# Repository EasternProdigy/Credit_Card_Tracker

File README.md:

# Wallet tracker card: handoff package (rev 0.5, 2026-11-13)

## How to use this
1. Copy everything in this folder into your KiCad project folder (e.g. `~/Desktop/PCB/<project>/`).
2. `CLAUDE.md` goes in the project root. Claude Code reads it automatically.
3. Set up git and the secret scanner once: `bash scripts/install_git_hooks.sh`, then `git add . && git commit -m "Add design handoff package rev 0.5"`
4. Start Claude Code in that folder and say: **"Read CLAUDE.md and docs/00_START_HERE.md, then start step 1."**

## Contents
- `CLAUDE.md`: role, rules and workflow for the KiCad Claude
- `docs/`: requirements, architecture, schematic spec, layout constraints, stackup, firmware, server, verification plan, open items, decision log
- `design/`: `netlist.yaml` (every part and net), `bom_v1.csv`, `bom_v2.csv`, `values_calc.py`
- `sims/`: every simulation and verification script, plus `results/` JSON
- `reports/`: research report and verification report
- `plots/`: simulation plots
- `server/`: Traccar config used in the backend test

## Rerun the sims on Fedora
```
sudo dnf install ngspice
pip install --user PyNEC numpy scipy matplotlib cryptography ecdsa pycryptodomex requests
cd sims && python3 qi_coupling.py && python3 power_path_ngspice.py   # etc.
```
`protocol_roundtrip.py` needs `git clone https://github.com/leonboe1/GoogleFindMyTools /tmp/src/GoogleFindMyTools`.
`backend_e2e.py` needs Traccar running with `server/traccar.xml`.

Design review page (3D model, floorplan, face, schematic draft): https://claude.ai/artifact/XV6vFWMy8m2t3a1oJFXLs5

## Auto-logging (open-source build log)
Every Claude Code session in this folder logs itself:
- `.claude/settings.json` registers two hooks. **SessionStart** loads the latest log so each session picks up where the last left off. **Stop** blocks Claude from finishing a turn if it changed files without writing to `docs/log/<today>.md`, or if raw data is sitting in `measurements/inbox/`.
- Drop PPK2 exports, NanoVNA `.s1p` files, scope screenshots and photos into `measurements/inbox/`. Claude files each into `measurements/<date>/` with a note and logs it (`scripts/log_measurement.py`).
- Tell Claude test results in plain words too; the rules in `CLAUDE.md` make it log them.
- Secrets live in `secrets/` (git-ignored), and the pre-commit hook runs gitleaks.
- Use the same folder (and `CLAUDE.md`) for the firmware, server and app sessions, under `firmware/`, `server/` and `app/`, so all of them write to one log.

Before making the repo public: pick licenses (common choice: CERN-OHL-S-2.0 for hardware, CC BY 4.0 for docs; firmware and server must match the upstream Everytag, GoogleFindMyTools and macless-haystack licenses), and add a README note that the unwanted-tracking alerts are kept on.

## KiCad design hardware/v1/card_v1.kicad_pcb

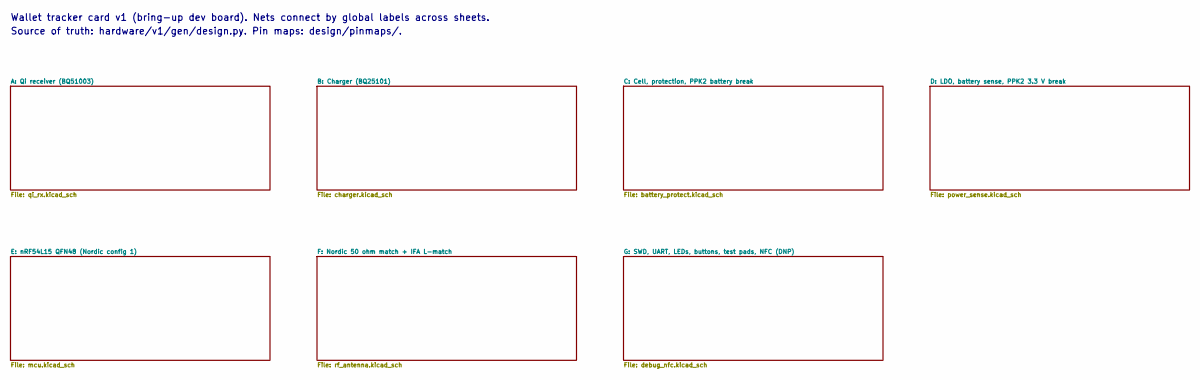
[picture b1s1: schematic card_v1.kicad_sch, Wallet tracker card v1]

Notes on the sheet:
Wallet tracker card v1 (bring-up dev board). Nets connect by global labels across sheets.
Source of truth: hardware/v1/gen/design.py. Pin maps: design/pinmaps/.

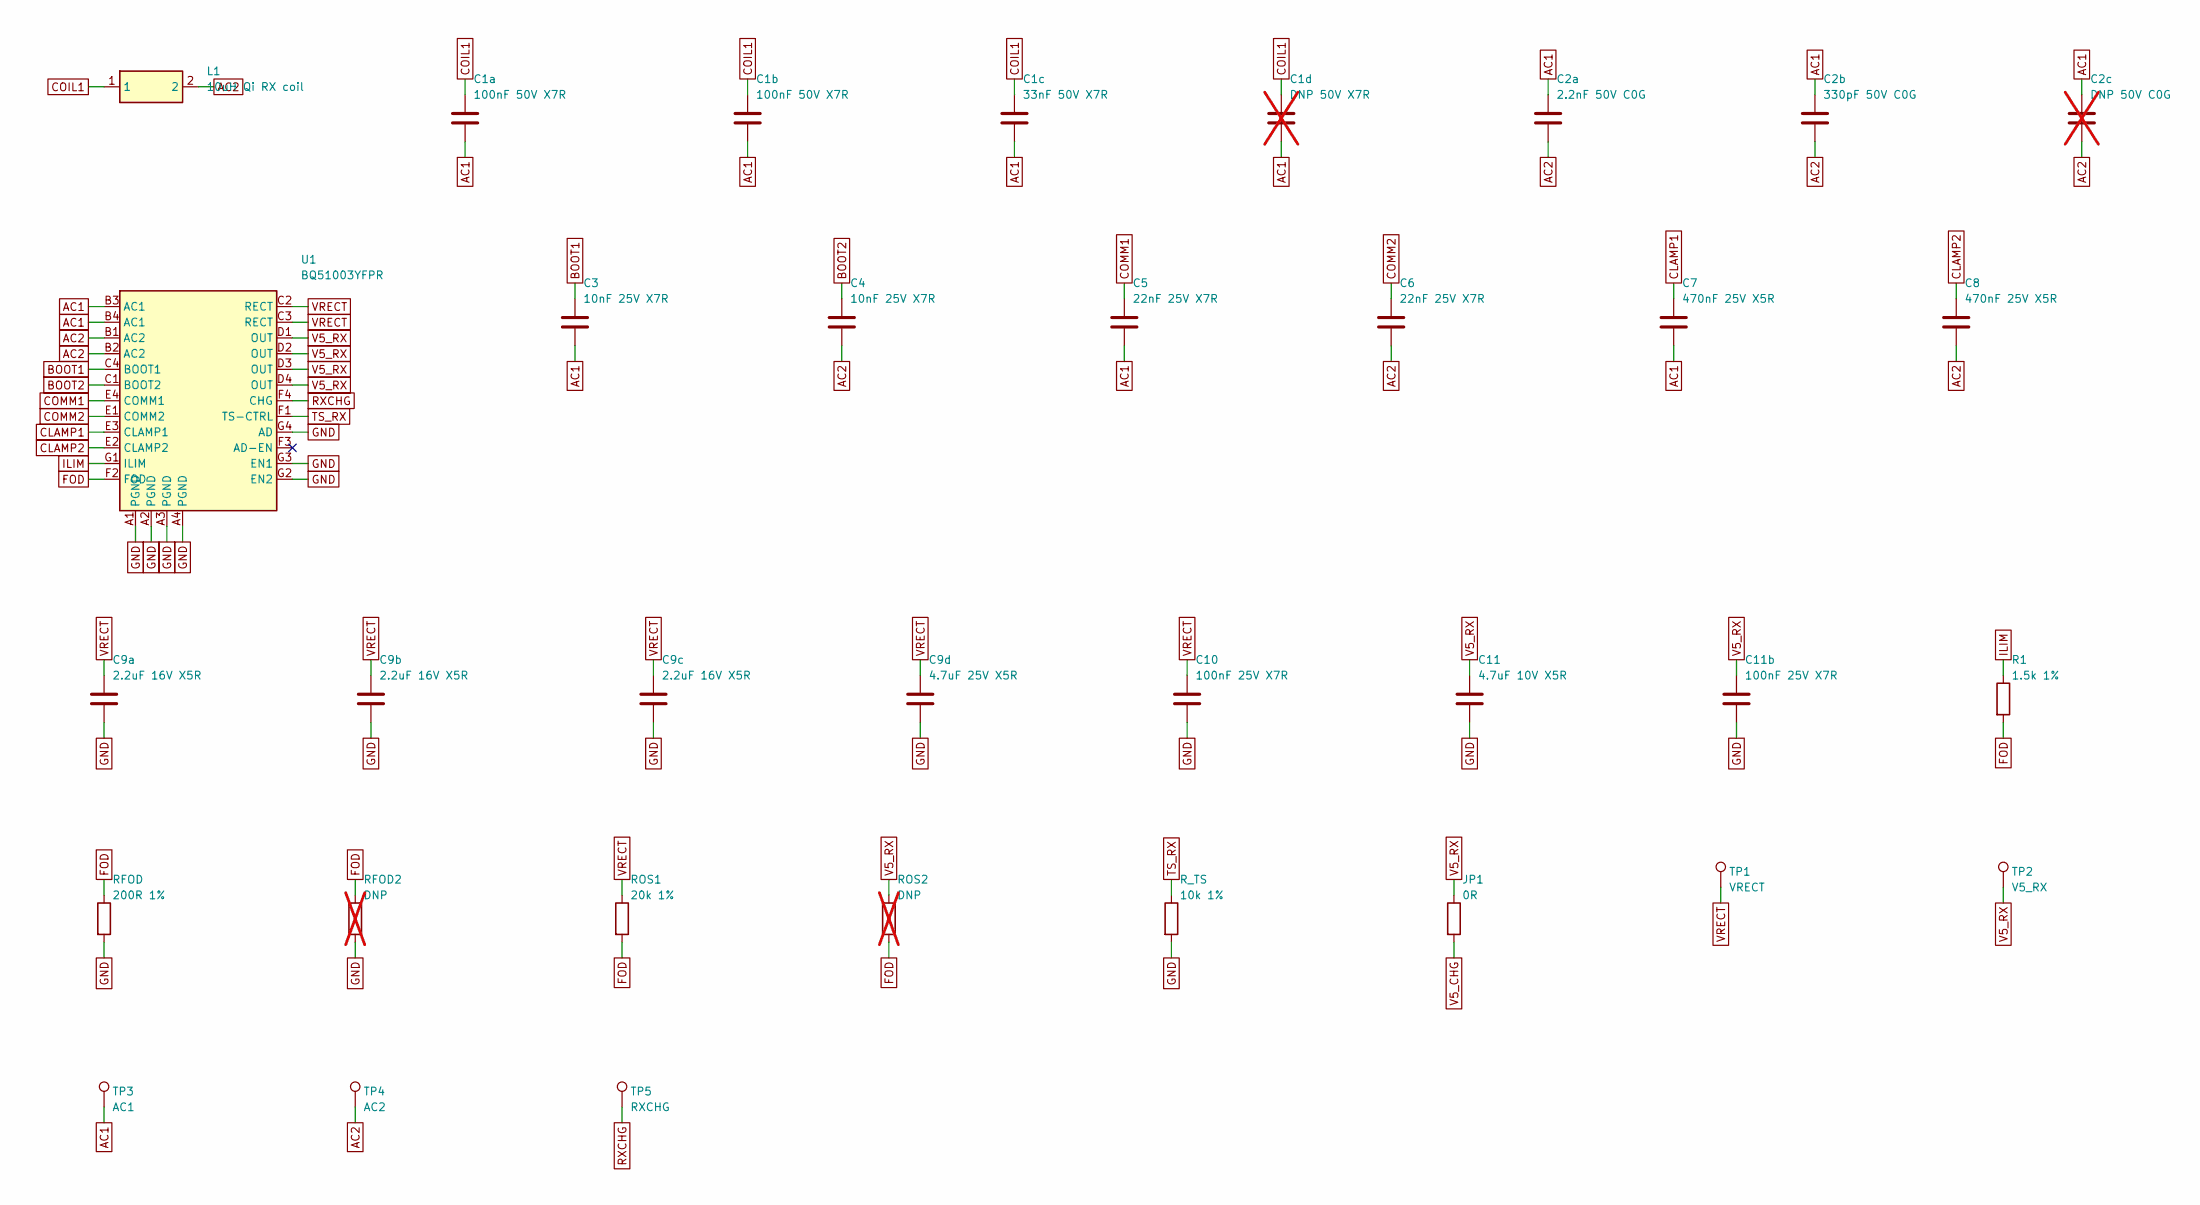
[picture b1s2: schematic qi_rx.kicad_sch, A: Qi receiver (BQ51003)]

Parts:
C1a, C1b: 100nF 50V X7R; C_0603_1608Metric; LCSC C14663
C1c: 33nF 50V X7R; C_0603_1608Metric; LCSC C21117
C1d: DNP 50V X7R; C_0603_1608Metric; not fitted
C2a: 2.2nF 50V C0G; C_0603_1608Metric; LCSC C107043
C2b: 330pF 50V C0G; C_0603_1608Metric; LCSC C1664
C2c: DNP 50V C0G; C_0603_1608Metric; not fitted
C3, C4: 10nF 25V X7R; C_0402_1005Metric; LCSC C15195
C5, C6: 22nF 25V X7R; C_0402_1005Metric; LCSC C1532
C7, C8: 470nF 25V X5R; C_0402_1005Metric; LCSC C437527
C9a, C9b, C9c: 2.2uF 16V X5R; C_0402_1005Metric; LCSC C386077
C9d: 4.7uF 25V X5R; C_0603_1608Metric; LCSC C69335
C10, C11b: 100nF 25V X7R; C_0402_1005Metric; LCSC C307331
C11: 4.7uF 10V X5R; C_0402_1005Metric; LCSC C23733
JP1: 0R; R_0603_1608Metric; LCSC C21189
L1: 10uH Qi RX coil; Wurth_760308101309_THT; MPN Wurth 760308101309
R1: 1.5k 1%; R_0402_1005Metric; LCSC C25867
RFOD: 200R 1%; R_0402_1005Metric; LCSC C25087
RFOD2: DNP; R_0402_1005Metric; not fitted
ROS1: 20k 1%; R_0402_1005Metric; LCSC C25765
ROS2: DNP; R_0402_1005Metric; not fitted
R_TS: 10k 1%; R_0402_1005Metric; LCSC C25744
TP1: VRECT; TestPoint_Pad_D1.0mm
TP2: V5_RX; TestPoint_Pad_D1.0mm
TP3: AC1; TestPoint_Pad_D1.0mm
TP4: AC2; TestPoint_Pad_D1.0mm
TP5: RXCHG; TestPoint_Pad_D1.0mm
U1: BQ51003YFPR; Texas_DSBGA-28_1.9x3mm_Layout4x7_P0.4mm; MPN TI BQ51003YFPR; LCSC C134093

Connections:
AC1: C1a.2, C1b.2, C1c.2, C1d.2, C2a.1, C2b.1, C2c.1, C3.2, C5.2, C7.2, TP3.1, U1.B3 (AC1), U1.B4 (AC1)
AC2: C2a.2, C2b.2, C2c.2, C4.2, C6.2, C8.2, L1.2, TP4.1, U1.B1 (AC2), U1.B2 (AC2)
BOOT1: C3.1, U1.C4 (BOOT1)
BOOT2: C4.1, U1.C1 (BOOT2)
CLAMP1: C7.1, U1.E3 (CLAMP1)
CLAMP2: C8.1, U1.E2 (CLAMP2)
COIL1: C1a.1, C1b.1, C1c.1, C1d.1, L1.1
COMM1: C5.1, U1.E4 (COMM1)
COMM2: C6.1, U1.E1 (COMM2)
FOD: R1.2, RFOD.1, RFOD2.1, ROS1.2, ROS2.2, U1.F2 (FOD)
GND: C9a.2, C9b.2, C9c.2, C9d.2, C10.2, C11.2, C11b.2, RFOD.2, RFOD2.2, R_TS.2, U1.A1 (PGND), U1.A2 (PGND), U1.A3 (PGND), U1.A4 (PGND), U1.G2 (EN2), U1.G3 (EN1), U1.G4 (AD); also elsewhere on the board
ILIM: R1.1, U1.G1 (ILIM)
RXCHG: TP5.1, U1.F4 (CHG)
TS_RX: R_TS.1, U1.F1 (TS-CTRL)
V5_CHG: JP1.2; also elsewhere on the board
V5_RX: C11.1, C11b.1, JP1.1, ROS2.1, TP2.1, U1.D1 (OUT), U1.D2 (OUT), U1.D3 (OUT), U1.D4 (OUT)
VRECT: C9a.1, C9b.1, C9c.1, C9d.1, C10.1, ROS1.1, TP1.1, U1.C2 (RECT), U1.C3 (RECT)

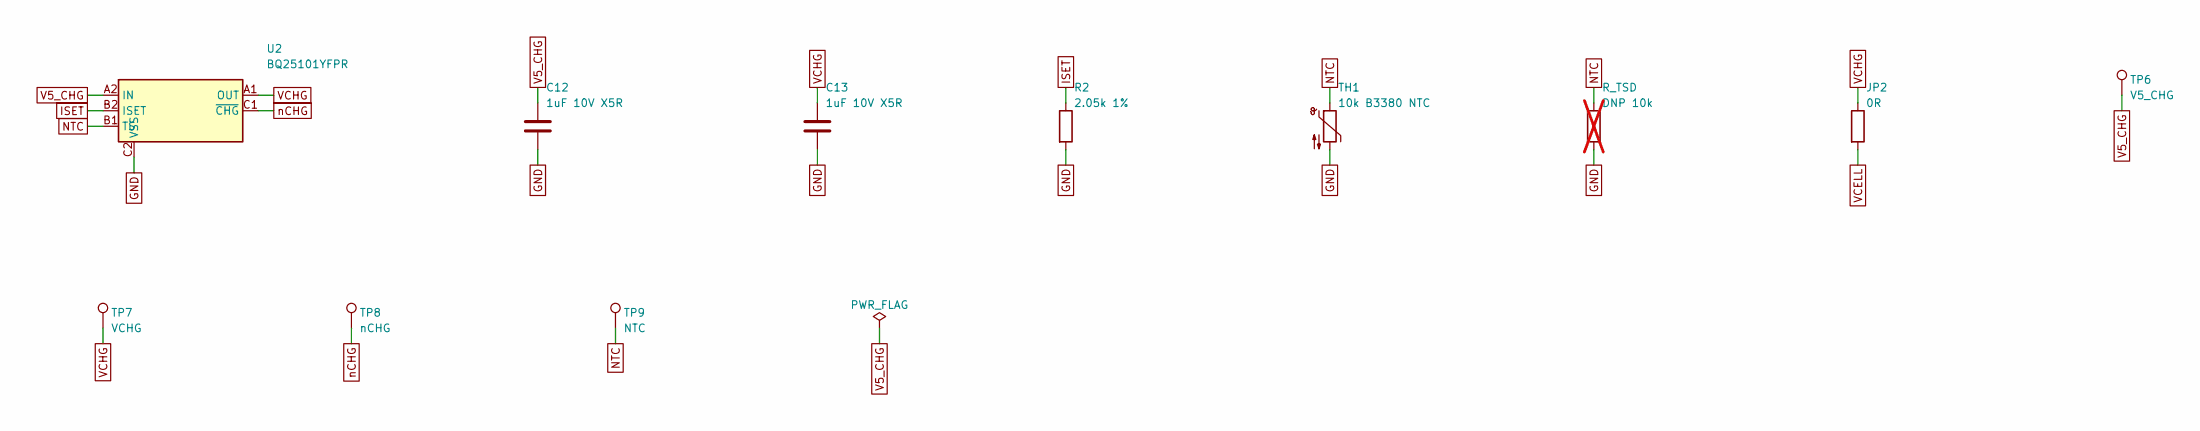
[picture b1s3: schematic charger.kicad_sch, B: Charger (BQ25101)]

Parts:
C12, C13: 1uF 10V X5R; C_0402_1005Metric; LCSC C52923
JP2: 0R; R_0603_1608Metric; LCSC C21189
R2: 2.05k 1%; R_0402_1005Metric; LCSC C226951
R_TSD: DNP 10k; R_0402_1005Metric; not fitted
TH1: 10k B3380 NTC; R_0402_1005Metric; MPN Murata NCP15XH103F03RC; LCSC C77131
TP6: V5_CHG; TestPoint_Pad_D1.0mm
TP7: VCHG; TestPoint_Pad_D1.0mm
TP8: nCHG; TestPoint_Pad_D1.0mm
TP9: NTC; TestPoint_Pad_D1.0mm
U2: BQ25101YFPR; Texas_DSBGA-6_0.95x1.488mm_Layout2x3_P0.4mm; MPN TI BQ25101YFPR; LCSC C478468

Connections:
GND: C12.2, C13.2, R2.2, R_TSD.2, TH1.2, U2.C2 (VSS); also elsewhere on the board
ISET: R2.1, U2.B2 (ISET)
NTC: R_TSD.1, TH1.1, TP9.1, U2.B1 (TS)
V5_CHG: C12.1, TP6.1, U2.A2 (IN); also elsewhere on the board
VCELL: JP2.2; also elsewhere on the board
VCHG: C13.1, JP2.1, TP7.1, U2.A1 (OUT)
nCHG: TP8.1, U2.C1 (~CHG); also elsewhere on the board

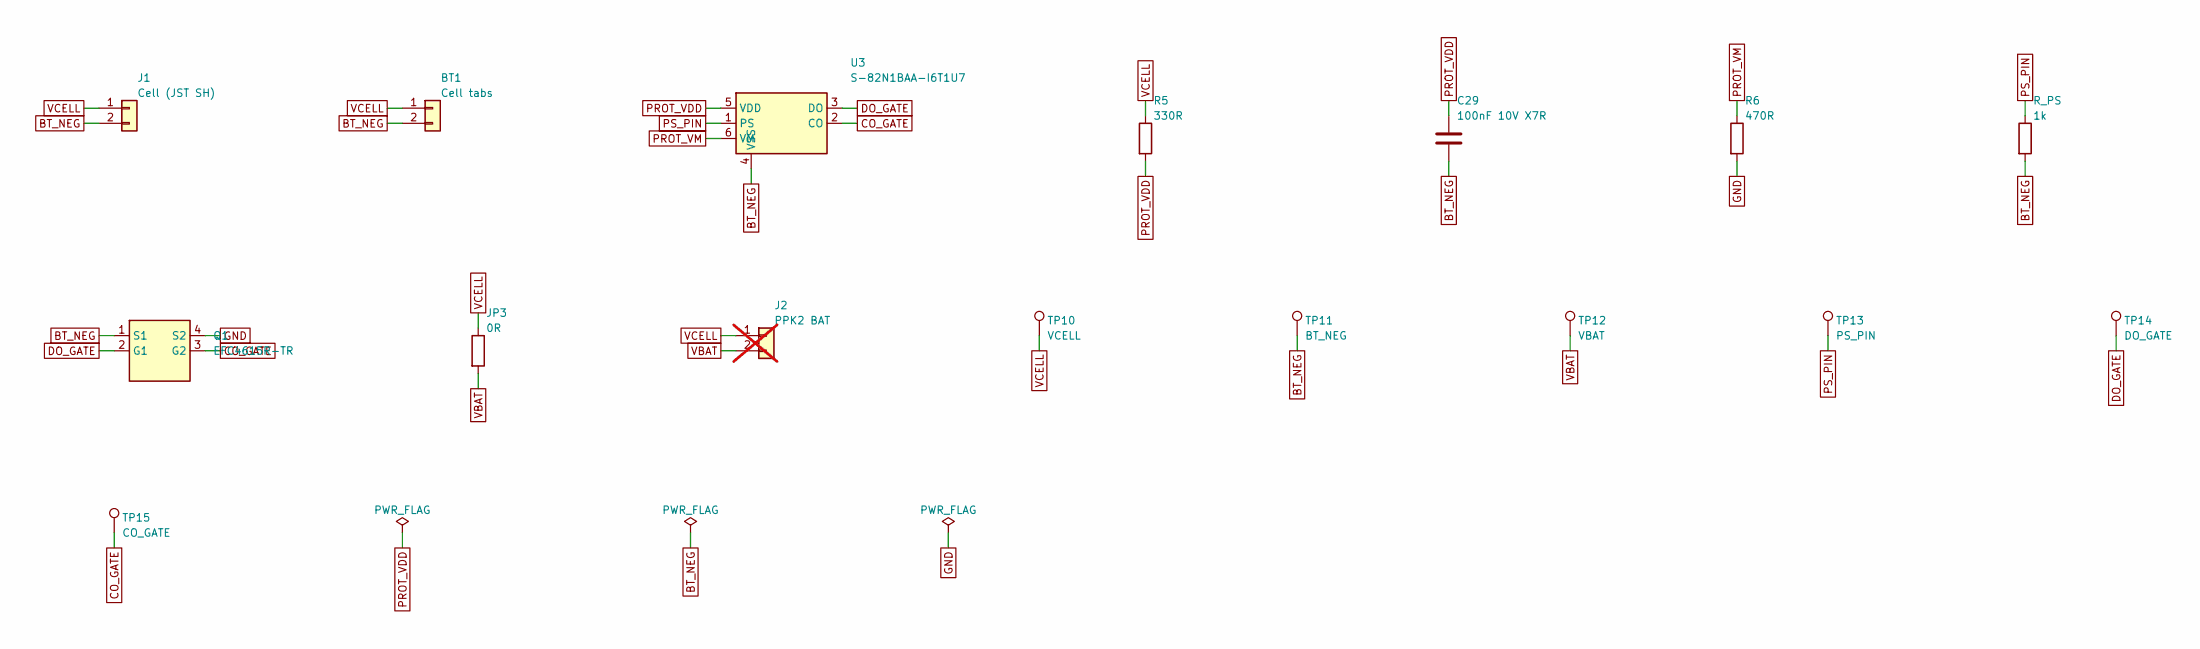
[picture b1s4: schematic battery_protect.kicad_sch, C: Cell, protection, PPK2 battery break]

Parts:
BT1: Cell tabs; Battery_Tabs_2x3mm
C29: 100nF 10V X7R; C_0402_1005Metric; LCSC C307331
J1: Cell (JST SH); JST_SH_SM02B-SRSS-TB_1x02-1MP_P1.00mm_Horizontal; MPN JST SM02B-SRSS-TB; LCSC C160402
J2: PPK2 BAT; PinHeader_1x02_P2.54mm_Vertical; not fitted
JP3: 0R; R_0603_1608Metric; LCSC C21189
Q1: EFC4615R-TR; onsemi_EFCP-4_1.46x1.46mm_P0.65mm; MPN onsemi EFC4615R-TR; LCSC C605382
R5: 330R; R_0402_1005Metric; LCSC C25104
R6: 470R; R_0402_1005Metric; LCSC C25117
R_PS: 1k; R_0402_1005Metric; LCSC C11702
TP10: VCELL; TestPoint_Pad_D1.0mm
TP11: BT_NEG; TestPoint_Pad_D1.0mm
TP12: VBAT; TestPoint_Pad_D1.0mm
TP13: PS_PIN; TestPoint_Pad_D1.0mm
TP14: DO_GATE; TestPoint_Pad_D1.0mm
TP15: CO_GATE; TestPoint_Pad_D1.0mm
U3: S-82N1BAA-I6T1U7; ABLIC_SNT-6A; MPN ABLIC S-82N1BAA-I6T1U7

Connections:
BT_NEG: BT1.2, C29.2, J1.2, Q1.1 (S1), R_PS.2, TP11.1, U3.4 (VSS)
CO_GATE: Q1.3 (G2), TP15.1, U3.2 (CO)
DO_GATE: Q1.2 (G1), TP14.1, U3.3 (DO)
GND: Q1.4 (S2), R6.2; also elsewhere on the board
PROT_VDD: C29.1, R5.2, U3.5 (VDD)
PROT_VM: R6.1, U3.6 (VM)
PS_PIN: R_PS.1, TP13.1, U3.1 (PS)
VBAT: J2.2, JP3.2, TP12.1; also elsewhere on the board
VCELL: BT1.1, J1.1, J2.1, JP3.1, R5.1, TP10.1; also elsewhere on the board

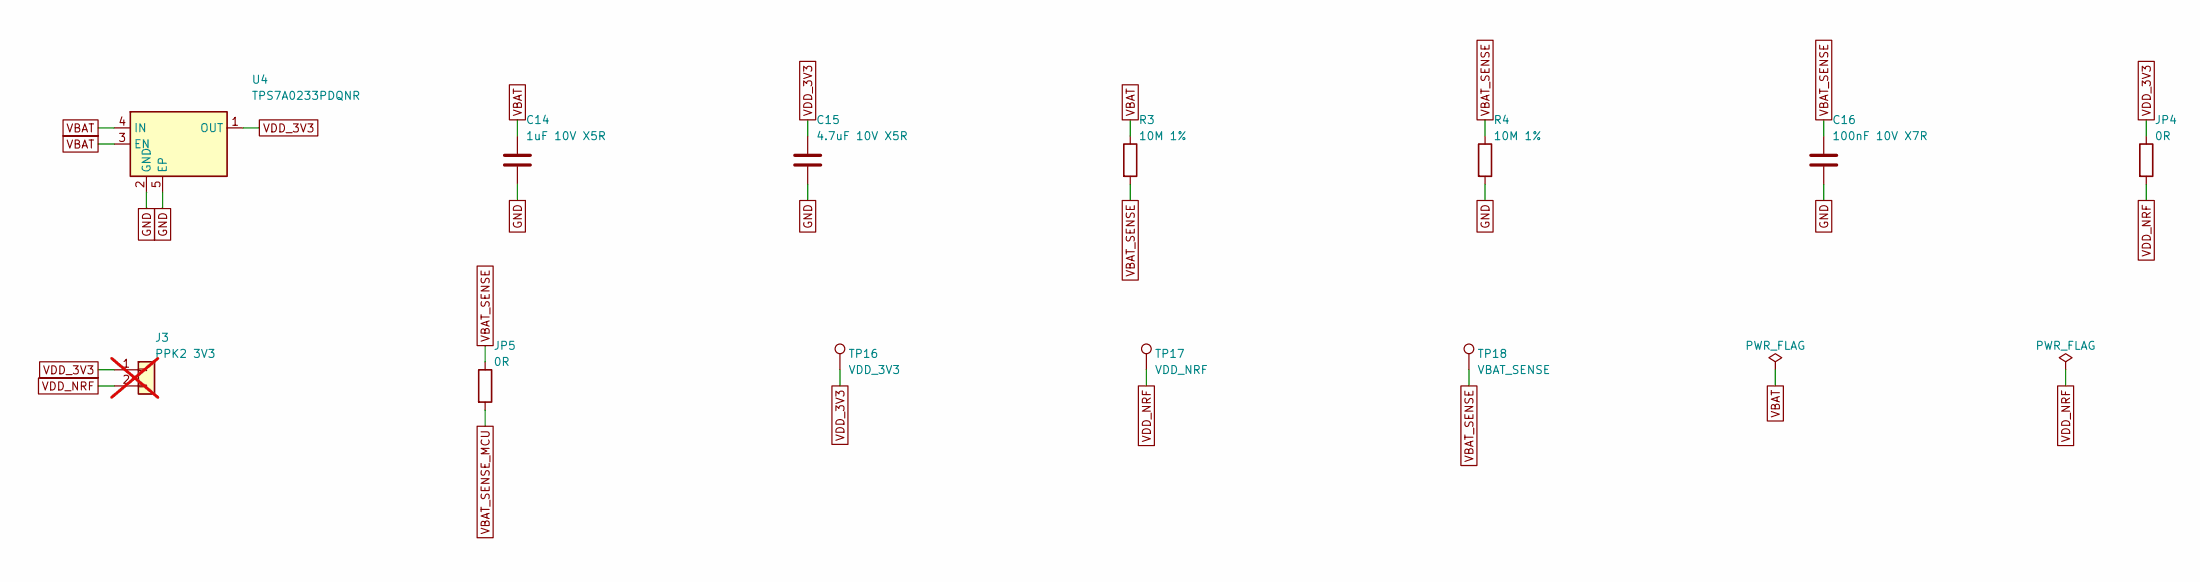
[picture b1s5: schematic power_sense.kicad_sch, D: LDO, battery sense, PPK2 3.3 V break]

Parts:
C14: 1uF 10V X5R; C_0402_1005Metric; LCSC C52923
C15: 4.7uF 10V X5R; C_0402_1005Metric; LCSC C23733
C16: 100nF 10V X7R; C_0402_1005Metric; LCSC C307331
J3: PPK2 3V3; PinHeader_1x02_P2.54mm_Vertical; not fitted
JP4: 0R; R_0603_1608Metric; LCSC C21189
JP5: 0R; R_0402_1005Metric; LCSC C17168
R3, R4: 10M 1%; R_0402_1005Metric; LCSC C321107
TP16: VDD_3V3; TestPoint_Pad_D1.0mm
TP17: VDD_NRF; TestPoint_Pad_D1.0mm
TP18: VBAT_SENSE; TestPoint_Pad_D1.0mm
U4: TPS7A0233PDQNR; Texas_X2SON-4_1x1mm_P0.65mm; MPN TI TPS7A0233PDQNR

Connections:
GND: C14.2, C15.2, C16.2, R4.2, U4.2 (GND), U4.5 (EP); also elsewhere on the board
VBAT: C14.1, R3.1, U4.3 (EN), U4.4 (IN); also elsewhere on the board
VBAT_SENSE: C16.1, JP5.1, R3.2, R4.1, TP18.1
VBAT_SENSE_MCU: JP5.2; also elsewhere on the board
VDD_3V3: C15.1, J3.1, JP4.1, TP16.1, U4.1 (OUT)
VDD_NRF: J3.2, JP4.2, TP17.1; also elsewhere on the board

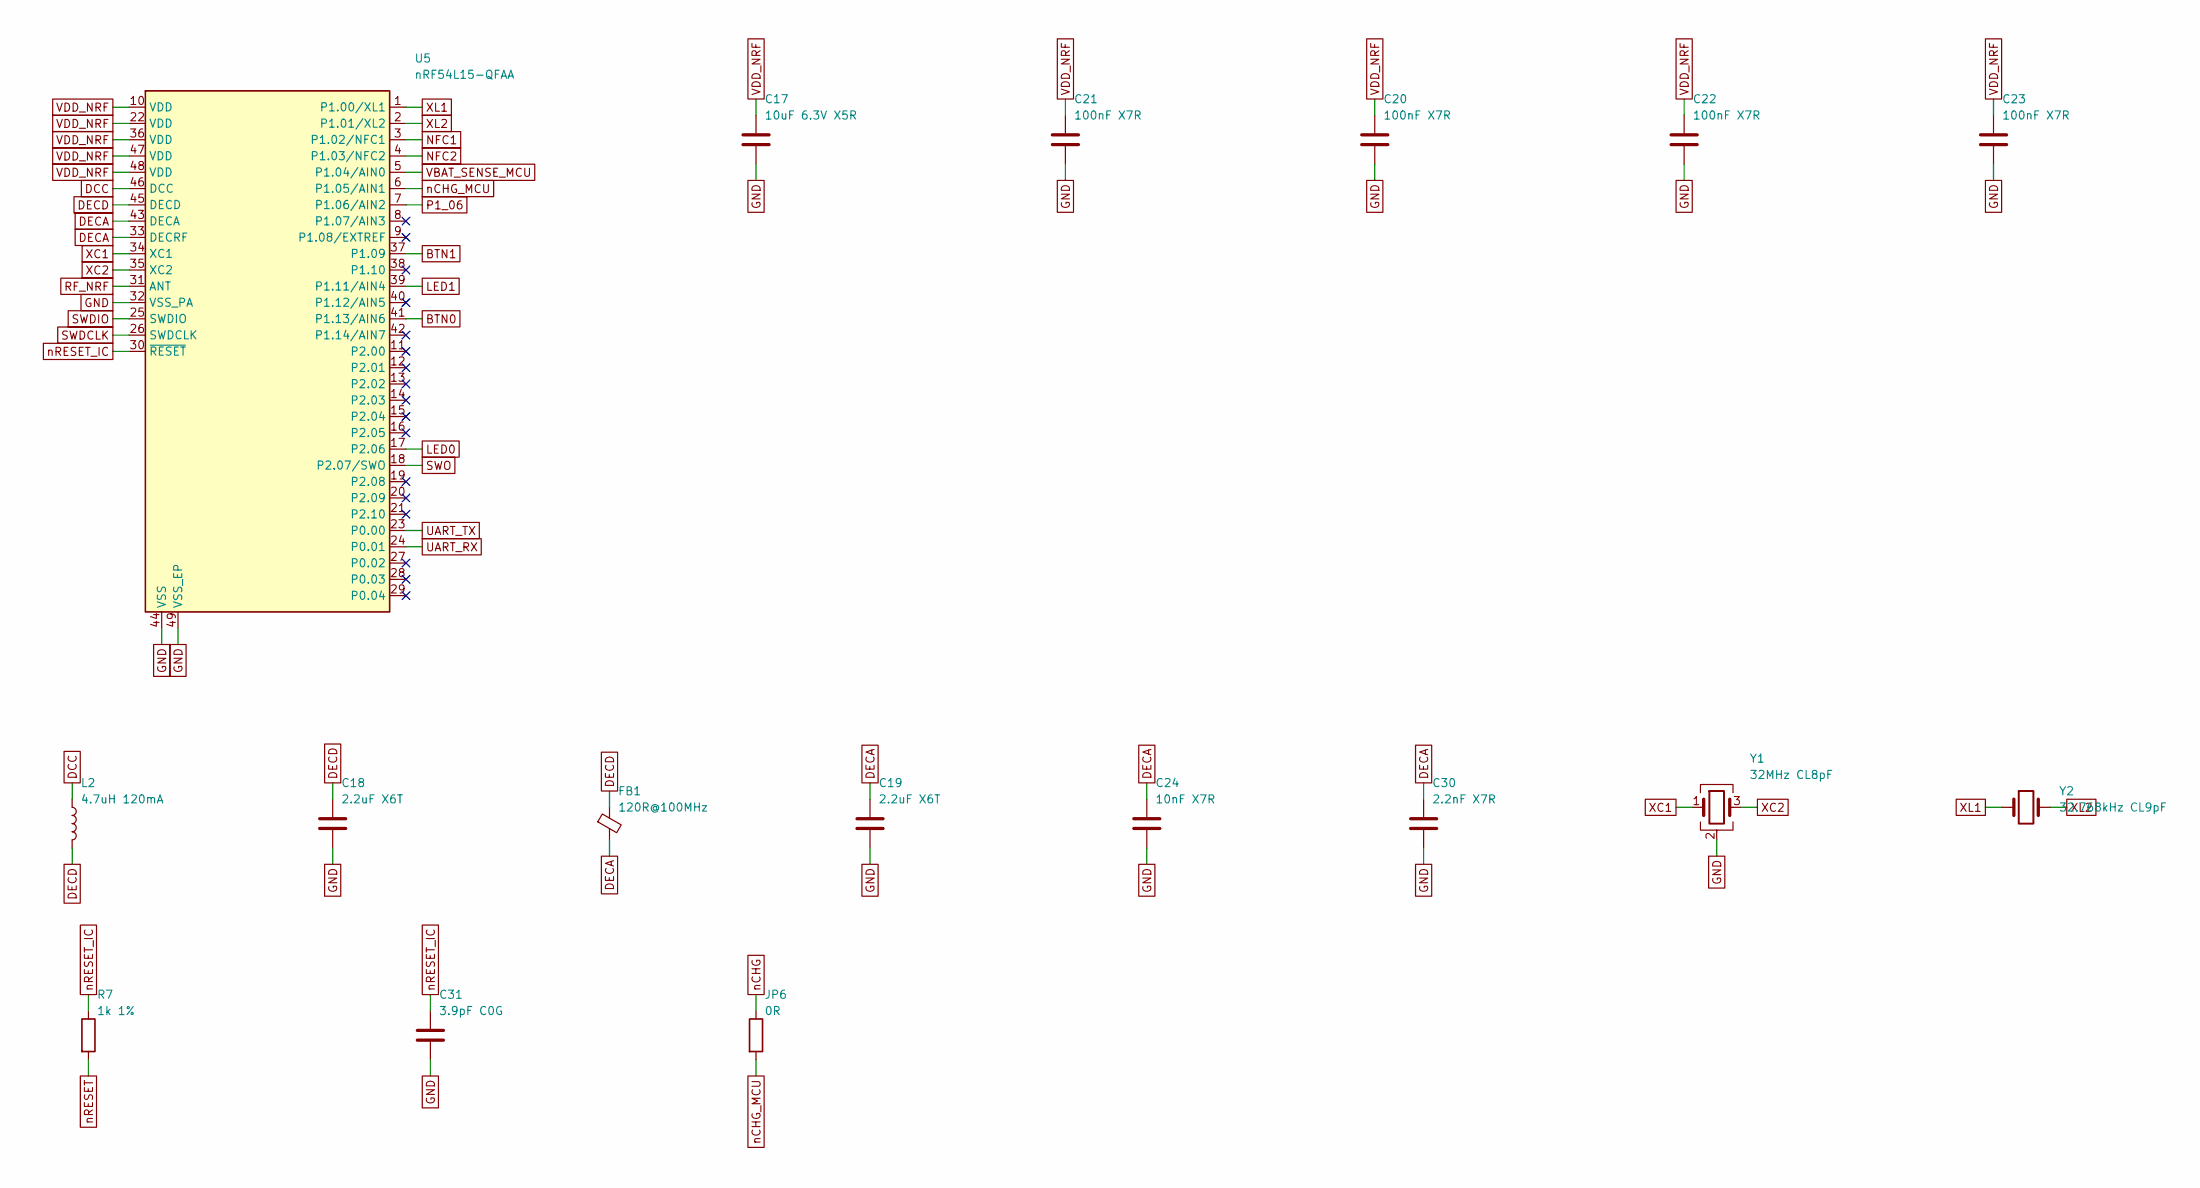
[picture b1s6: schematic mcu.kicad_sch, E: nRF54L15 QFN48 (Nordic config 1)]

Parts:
C17: 10uF 6.3V X5R; C_0402_1005Metric; LCSC C15525
C18, C19: 2.2uF X6T; C_0201_0603Metric; LCSC C386031
C20, C21, C22, C23: 100nF X7R; C_0201_0603Metric; LCSC C85923
C24: 10nF X7R; C_0201_0603Metric; LCSC C285010
C30: 2.2nF X7R; C_0201_0603Metric; LCSC C80433
C31: 3.9pF C0G; C_0201_0603Metric; LCSC C76926
FB1: 120R@100MHz; L_0201_0603Metric; LCSC C525479
JP6: 0R; R_0402_1005Metric; LCSC C17168
L2: 4.7uH 120mA; L_0603_1608Metric; MPN Murata LQM18PN4R7MFRL; LCSC C114862
R7: 1k 1%; R_0201_0603Metric; LCSC C270365
U5: nRF54L15-QFAA; QFN-48-1EP_6x6mm_P0.4mm_EP4.6x4.6mm; MPN Nordic nRF54L15-QFAA-R7; LCSC C42458750
Y1: 32MHz CL8pF; Crystal_SMD_2016-4Pin_2.0x1.6mm; MPN Murata XRCGB32M000F1S1BR0; LCSC C6938063
Y2: 32.768kHz CL9pF; Crystal_SMD_2012-2Pin_2.0x1.2mm; LCSC C96341

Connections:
BTN0: U5.41 (P1.13/AIN6); also elsewhere on the board
BTN1: U5.37 (P1.09); also elsewhere on the board
DCC: L2.1, U5.46 (DCC)
DECA: C19.1, C24.1, C30.1, FB1.2, U5.33 (DECRF), U5.43 (DECA)
DECD: C18.1, FB1.1, L2.2, U5.45 (DECD)
GND: C17.2, C18.2, C19.2, C20.2, C21.2, C22.2, C23.2, C24.2, C30.2, C31.2, U5.32 (VSS_PA), U5.44 (VSS), U5.49 (VSS_EP), Y1.2 (G), Y1.4 (G); also elsewhere on the board
LED0: U5.17 (P2.06); also elsewhere on the board
LED1: U5.39 (P1.11/AIN4); also elsewhere on the board
NFC1: U5.3 (P1.02/NFC1); also elsewhere on the board
NFC2: U5.4 (P1.03/NFC2); also elsewhere on the board
P1_06: U5.7 (P1.06/AIN2); also elsewhere on the board
RF_NRF: U5.31 (ANT); also elsewhere on the board
SWDCLK: U5.26 (SWDCLK); also elsewhere on the board
SWDIO: U5.25 (SWDIO); also elsewhere on the board
SWO: U5.18 (P2.07/SWO); also elsewhere on the board
UART_RX: U5.24 (P0.01); also elsewhere on the board
UART_TX: U5.23 (P0.00); also elsewhere on the board
VBAT_SENSE_MCU: U5.5 (P1.04/AIN0); also elsewhere on the board
VDD_NRF: C17.1, C20.1, C21.1, C22.1, C23.1, U5.10 (VDD), U5.22 (VDD), U5.36 (VDD), U5.47 (VDD), U5.48 (VDD); also elsewhere on the board
XC1: U5.34 (XC1), Y1.1
XC2: U5.35 (XC2), Y1.3
XL1: U5.1 (P1.00/XL1), Y2.1
XL2: U5.2 (P1.01/XL2), Y2.2
nCHG: JP6.1; also elsewhere on the board
nCHG_MCU: JP6.2, U5.6 (P1.05/AIN1)
nRESET: R7.2; also elsewhere on the board
nRESET_IC: C31.1, R7.1, U5.30 (~RESET)

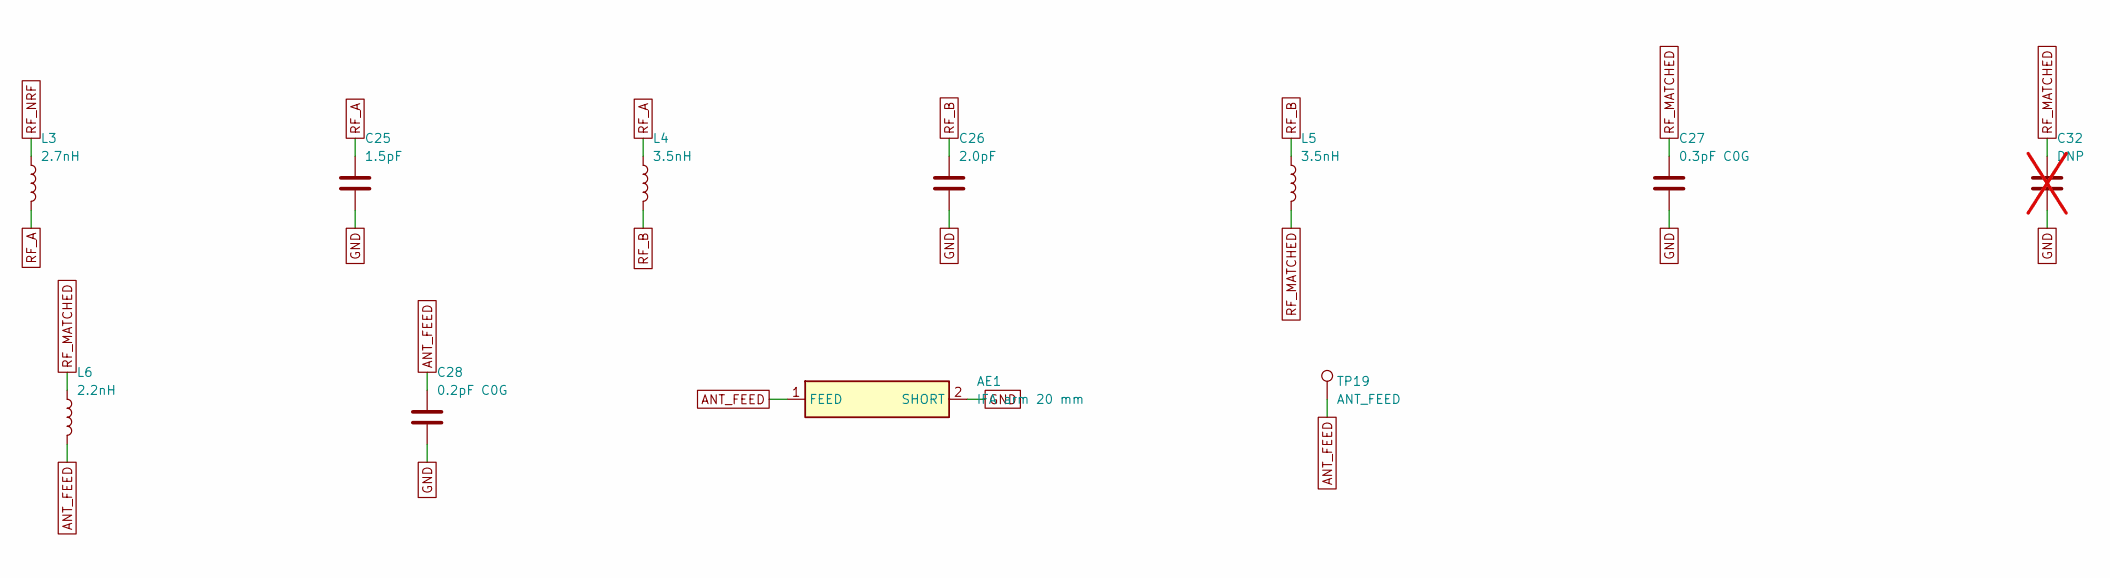
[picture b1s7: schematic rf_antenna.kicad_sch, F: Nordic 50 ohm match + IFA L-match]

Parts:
AE1: IFA arm 20 mm; IFA_2G4_arm20_h6
C25: 1.5pF; C_0201_0603Metric; MPN Murata GJM0335C1E1R5WB01; LCSC C435397
C26: 2.0pF; C_0201_0603Metric; MPN Murata GJM0335C1E2R0WB01; LCSC C668326
C27: 0.3pF C0G; C_0201_0603Metric; LCSC C76927
C28: 0.2pF C0G; C_0201_0603Metric; LCSC C913527
C32: DNP; C_0201_0603Metric; not fitted
L3: 2.7nH; L_0201_0603Metric; MPN Murata LQP03HQ2N7B02; LCSC C7216765
L4, L5: 3.5nH; L_0201_0603Metric; MPN Murata LQP03TN3N5B02; LCSC C206424
L6: 2.2nH; L_0201_0603Metric; LCSC C98041
TP19: ANT_FEED; TestPoint_Pad_D0.6mm

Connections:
ANT_FEED: AE1.1 (FEED), C28.1, L6.2, TP19.1
GND: AE1.2 (SHORT), C25.2, C26.2, C27.2, C28.2, C32.2; also elsewhere on the board
RF_A: C25.1, L3.2, L4.1
RF_B: C26.1, L4.2, L5.1
RF_MATCHED: C27.1, C32.1, L5.2, L6.1
RF_NRF: L3.1; also elsewhere on the board

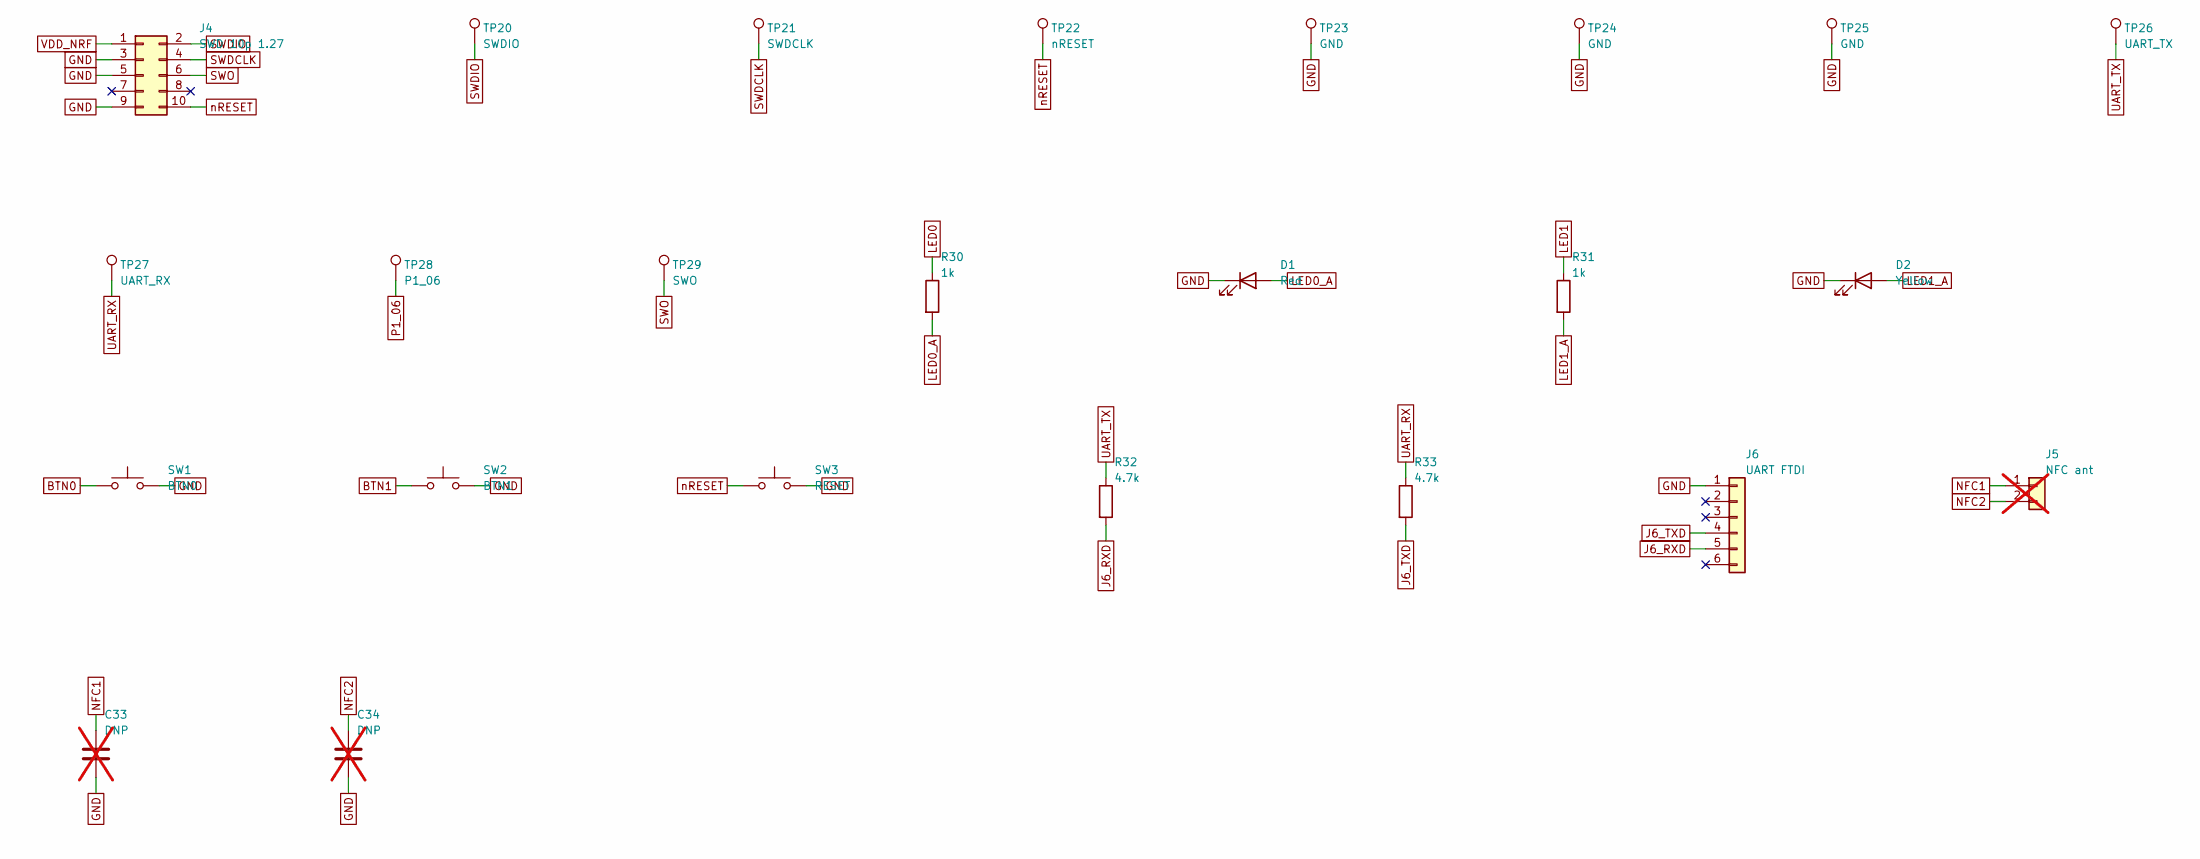
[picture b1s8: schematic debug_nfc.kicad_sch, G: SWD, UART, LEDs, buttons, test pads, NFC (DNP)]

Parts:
C33, C34: DNP; C_0402_1005Metric; not fitted
D1: Red; LED_0603_1608Metric; MPN KENTO KT-0603R; LCSC C2286
D2: Yellow; LED_0603_1608Metric; MPN NationStar NCD0603Y2; LCSC C89811
J4: SWD 10p 1.27; PinHeader_2x05_P1.27mm_Vertical_SMD; MPN Cortex Debug 10-pin; LCSC C598540
J5: NFC ant; PinHeader_1x02_P2.54mm_Vertical; not fitted
J6: UART FTDI; PinHeader_1x06_P2.54mm_Vertical; MPN 2.54 mm 1x6 header; LCSC C37208
R30, R31: 1k; R_0402_1005Metric; LCSC C11702
R32, R33: 4.7k; R_0402_1005Metric; LCSC C25900
SW1: BTN0; SW_Push_1P1T_XKB_TS-1187A; MPN XKB TS-1187A-B-A-B; LCSC C318884
SW2: BTN1; SW_Push_1P1T_XKB_TS-1187A; MPN XKB TS-1187A-B-A-B; LCSC C318884
SW3: RESET; SW_Push_1P1T_XKB_TS-1187A; MPN XKB TS-1187A-B-A-B; LCSC C318884
TP20: SWDIO; TestPoint_Pad_D1.0mm
TP21: SWDCLK; TestPoint_Pad_D1.0mm
TP22: nRESET; TestPoint_Pad_D1.0mm
TP23, TP24, TP25: GND; TestPoint_Pad_D1.0mm
TP26: UART_TX; TestPoint_Pad_D1.0mm
TP27: UART_RX; TestPoint_Pad_D1.0mm
TP28: P1_06; TestPoint_Pad_D1.0mm
TP29: SWO; TestPoint_Pad_D1.0mm

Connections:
BTN0: SW1.1; also elsewhere on the board
BTN1: SW2.1; also elsewhere on the board
GND: C33.2, C34.2, D1.1 (K), D2.1 (K), J4.3, J4.5, J4.9, J6.1, SW1.2, SW2.2, SW3.2, TP23.1, TP24.1, TP25.1; also elsewhere on the board
J6_RXD: J6.5, R32.2
J6_TXD: J6.4, R33.2
LED0: R30.1; also elsewhere on the board
LED0_A: D1.2 (A), R30.2
LED1: R31.1; also elsewhere on the board
LED1_A: D2.2 (A), R31.2
NFC1: C33.1, J5.1; also elsewhere on the board
NFC2: C34.1, J5.2; also elsewhere on the board
P1_06: TP28.1; also elsewhere on the board
SWDCLK: J4.4, TP21.1; also elsewhere on the board
SWDIO: J4.2, TP20.1; also elsewhere on the board
SWO: J4.6, TP29.1; also elsewhere on the board
UART_RX: R33.1, TP27.1; also elsewhere on the board
UART_TX: R32.1, TP26.1; also elsewhere on the board
VDD_NRF: J4.1; also elsewhere on the board
nRESET: J4.10, SW3.1, TP22.1; also elsewhere on the board

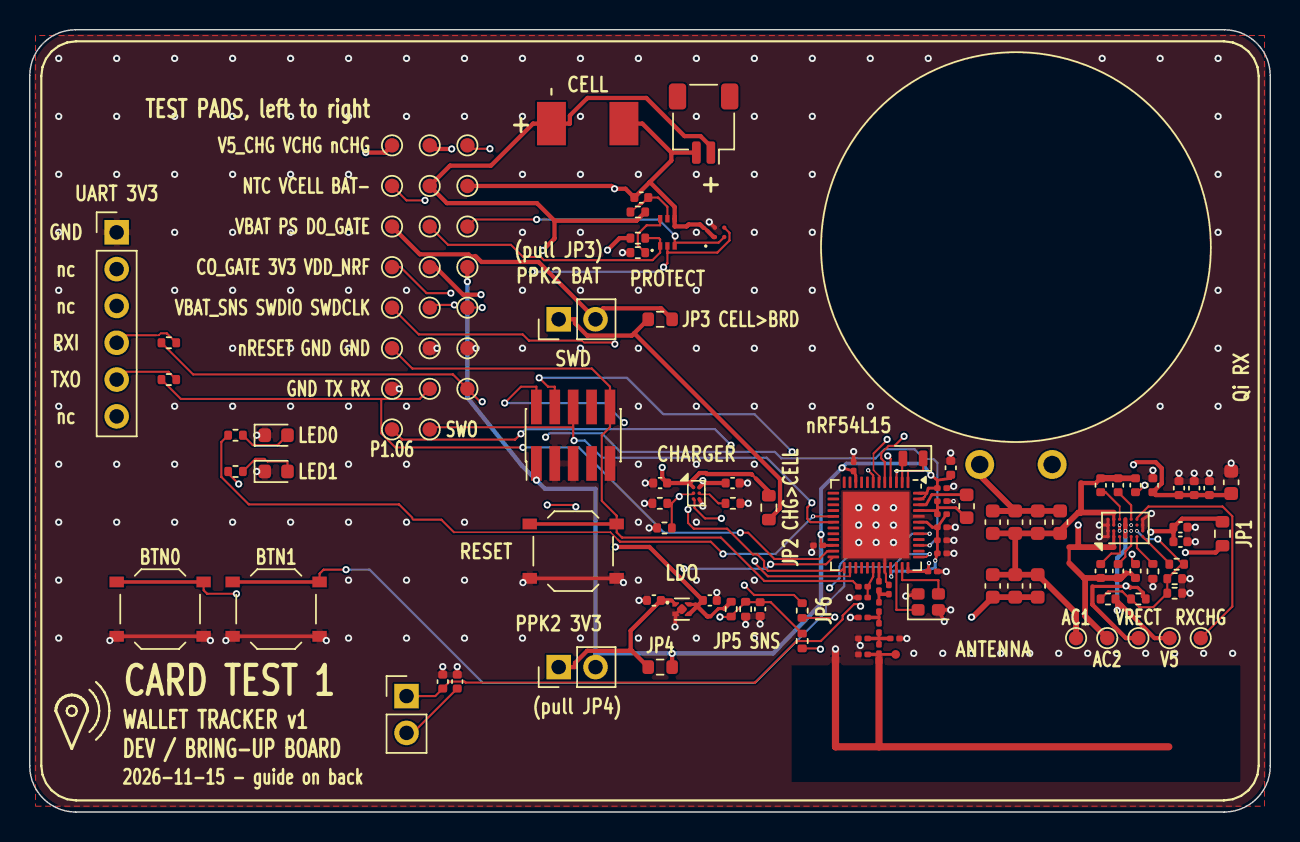
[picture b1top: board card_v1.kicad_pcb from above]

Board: 4 copper layers, 85.6 x 54.0 mm, 125 parts (0 on the bottom side), 64 nets.
